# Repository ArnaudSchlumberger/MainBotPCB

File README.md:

# MainBotPCB

This project is part of Robot Télécom Strasbourg's work as part of our participation to the French Robot Cup.

See our Github page here: https://github.com/AssociationRobotTelecomStrasbourg

And our website (quite empty yet :/ ) here :https://associationrobottelecomstrasbourg.github.io/

MainBotPCB is the PCB that will contain the majority of the  components and connections required for our main robot to work, hence the original name :) .

NotesConception.md contains my notes while working on this project (in French)

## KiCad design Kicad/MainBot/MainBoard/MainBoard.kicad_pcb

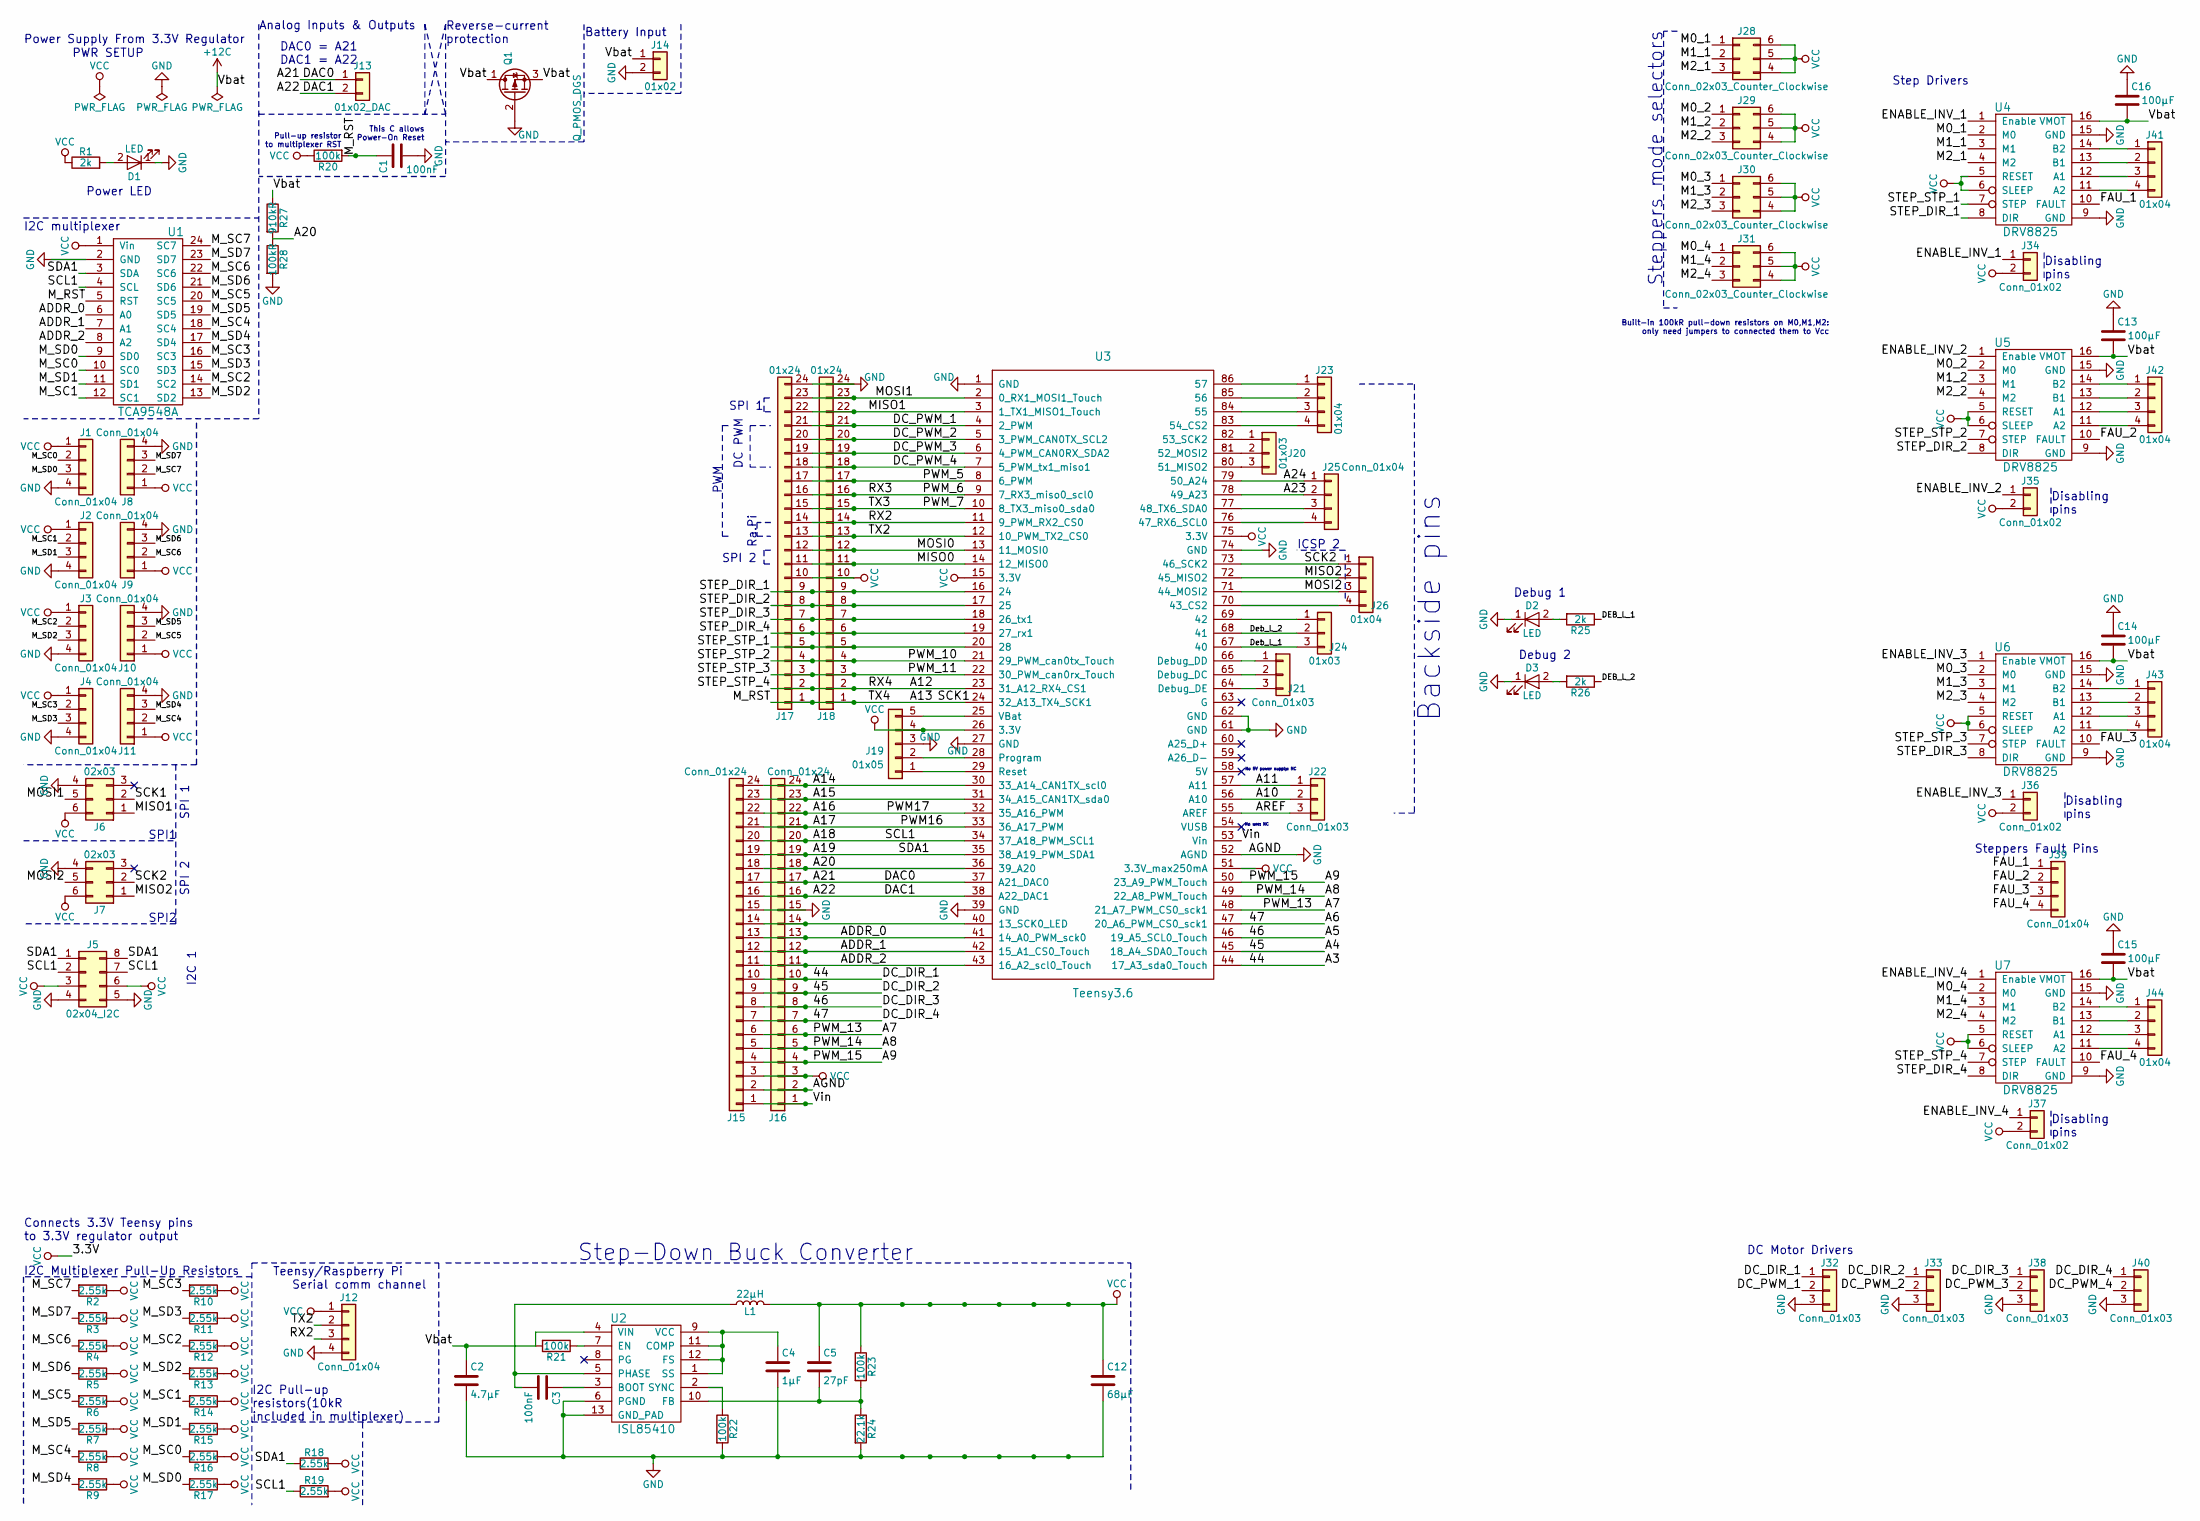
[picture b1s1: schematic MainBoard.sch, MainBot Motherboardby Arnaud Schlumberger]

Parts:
C1, C3: 100nF; C_1206_HandSoldering
C2: 4.7µF; C_1206_HandSoldering
C4: 1µF; C_1206_HandSoldering
C5: 27pF; C_1206_HandSoldering
C12: 68µF; CP_Elec_6.3x7.7
C13, C14, C15, C16: 100µF; CP_Radial_D6.3mm_P2.50mm
D1, D2, D3: LED; LED_1206
J1, J2, J3, J4, J8, J9, J10, J11, J12, J39: Conn_01x04; JST_XH_B04B-XH-A_04x2.50mm_Straight
J5: 02x04_I2C; Pin_Header_Straight_2x04_Pitch2.54mm
J6, J7: 02x03; Pin_Header_Straight_2x03_Pitch2.54mm
J13: 01x02_DAC; Pin_Header_Straight_1x02_Pitch2.54mm
J14: 01x02; BatConn
J15, J16: Conn_01x24; Socket_Strip_Straight_1x24_Pitch2.54mm
J17, J18: 01x24; Socket_Strip_Straight_1x24_Pitch2.54mm
J19: 01x05; Pin_Header_Straight_1x05_Pitch2.54mm
J20, J24: 01x03; Pin_Header_Straight_1x03_Pitch2.54mm
J21, J22: Conn_01x03; Pin_Header_Straight_1x03_Pitch2.54mm
J23, J26: 01x04; Pin_Header_Straight_1x04_Pitch2.54mm
J25: Conn_01x04; Pin_Header_Straight_1x04_Pitch2.54mm
J28, J29, J30, J31: Conn_02x03_Counter_Clockwise; Pin_Header_Straight_2x03_Pitch2.54mm
J32, J33, J38, J40: Conn_01x03; JST_XH_B03B-XH-A_03x2.50mm_Straight
J34, J35, J36, J37: Conn_01x02; Pin_Header_Straight_1x02_Pitch2.54mm
J41, J42, J43, J44: 01x04; JST_XH_B04B-XH-A_04x2.50mm_Straight
L1: 22µH; L1
Q1: Q_PMOS_DGS; SOT-23
R1, R25, R26: 2k; R_1206_HandSoldering
R2, R3, R4, R5, R6, R7, R8, R9, R10, R11, R12, R13, R14, R15, R16, R17, R18, R19: 2.55k; R_0805_HandSoldering
R20, R21, R22, R23: 100k; R_1206_HandSoldering
R24: 22.1k; R_1206_HandSoldering
R27: 910kR; R_1206_HandSoldering
R28: 100kR; R_1206_HandSoldering
U1: TCA9548A; TCA9548A_TSSOP
U2: ISL85410; DFN-12_DE-M
U3: Teensy3.6; Teensy35_36
U4, U5, U6, U7: DRV8825

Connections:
+12C: C2.1, C13.2, C14.2, C15.2, C16.2, J14.1, Q1.1 (D), Q1.3 (S), R21.2, R27.1, U2.4 (VIN), U4.16 (VMOT), U5.16 (VMOT), U6.16 (VMOT), U7.16 (VMOT)
/44: J15.10, J16.10, J32.1, U3.44 (17_A3_sda0_Touch)
/45: J15.9, J16.9, J33.1, U3.45 (18_A4_SDA0_Touch)
/46: J15.8, J16.8, J38.1, U3.46 (19_A5_SCL0_Touch)
/47: J15.7, J16.7, J40.1, U3.47 (20_A6_PWM_CS0_sck1)
/A7: J15.6, J16.6, U3.48 (21_A7_PWM_CS0_sck1)
/A8: J15.5, J16.5, U3.49 (22_A8_PWM_Touch)
/A9: J15.4, J16.4, U3.50 (23_A9_PWM_Touch)
/A10: J22.2, U3.56 (A10)
/A11: J22.1, U3.57 (A11)
/A12: J17.2, J18.2, U3.23 (31_A12_RX4_CS1), U7.7 (STEP)
/A13: C1.1, J6.2, J17.1, J18.1, R20.2, U1.5 (RST), U3.24 (32_A13_TX4_SCK1)
/A14: J15.24, J16.24, U3.30 (33_A14_CAN1TX_scl0)
/A15: J15.23, J16.23, U3.31 (34_A15_CAN1TX_sda0)
/A16: J15.22, J16.22, U3.32 (35_A16_PWM)
/A17: J15.21, J16.21, U3.33 (36_A17_PWM)
/A18: J5.2, J5.7, J15.20, J16.20, R19.1, U1.4 (SCL), U3.34 (37_A18_PWM_SCL1)
/A19: J5.1, J5.8, J15.19, J16.19, R18.1, U1.3 (SDA), U3.35 (38_A19_PWM_SDA1)
/A20: J15.18, J16.18, R27.2, R28.1, U3.36 (39_A20)
/A21: J13.1, J15.17, J16.17, U3.37 (A21_DAC0)
/A22: J13.2, J15.16, J16.16, U3.38 (A22_DAC1)
/A23: J25.2, U3.78 (49_A23)
/A24: J25.1, U3.79 (50_A24)
/ADDR_0: J15.13, J16.13, U1.6 (A0), U3.41 (14_A0_PWM_sck0)
/ADDR_1: J15.12, J16.12, U1.7 (A1), U3.42 (15_A1_CS0_Touch)
/ADDR_2: J15.11, J16.11, U1.8 (A2), U3.43 (16_A2_scl0_Touch)
/AREF: J22.3, U3.55 (AREF)
/DC_PWM_1: J17.21, J18.21, J32.2, U3.4 (2_PWM)
/DC_PWM_2: J17.20, J18.20, J33.2, U3.5 (3_PWM_CAN0TX_SCL2)
/DC_PWM_3: J17.19, J18.19, J38.2, U3.6 (4_PWM_CAN0RX_SDA2)
/DC_PWM_4: J17.18, J18.18, J40.2, U3.7 (5_PWM_tx1_miso1)
/DEB_L_1: J24.3, R25.1, U3.67 (40)
/DEB_L_2: J24.2, R26.1, U3.68 (41)
/ENABLE_INV_1: J34.1, U4.1 (Enable)
/ENABLE_INV_2: J35.1, U5.1 (Enable)
/ENABLE_INV_3: J36.1, U6.1 (Enable)
/ENABLE_INV_4: J37.1, U7.1 (Enable)
/FAU_1: J39.1, U4.10 (FAULT)
/FAU_2: J39.2, U5.10 (FAULT)
/FAU_3: J39.3, U6.10 (FAULT)
/FAU_4: J39.4, U7.10 (FAULT)
/M0_1: J28.1, U4.2 (M0)
/M0_2: J29.1, U5.2 (M0)
/M0_3: J30.1, U6.2 (M0)
/M0_4: J31.1, U7.2 (M0)
/M1_1: J28.2, U4.3 (M1)
/M1_2: J29.2, U5.3 (M1)
/M1_3: J30.2, U6.3 (M1)
/M1_4: J31.2, U7.3 (M1)
/M2_1: J28.3, U4.4 (M2)
/M2_2: J29.3, U5.4 (M2)
/M2_3: J30.3, U6.4 (M2)
/M2_4: J31.3, U7.4 (M2)
/MISO0: J17.11, J18.11, U3.14 (12_MISO0)
/MISO1: J6.1, J17.22, J18.22, U3.3 (1_TX1_MISO1_Touch)
/MISO2: J7.1, J26.2, U3.72 (45_MISO2)
/MOSI0: J17.12, J18.12, U3.13 (11_MOSI0)
/MOSI1: J6.5, J17.23, J18.23, U3.2 (0_RX1_MOSI1_Touch)
/MOSI2: J7.5, J26.3, U3.71 (44_MOSI2)
/M_SC0: J1.2, R16.2, U1.10 (SC0)
/M_SC1: J2.2, R14.2, U1.12 (SC1)
/M_SC2: J3.2, R12.2, U1.14 (SC2)
/M_SC3: J4.2, R10.2, U1.16 (SC3)
/M_SC4: J11.2, R8.2, U1.18 (SC4)
/M_SC5: J10.2, R6.2, U1.20 (SC5)
/M_SC6: J9.2, R4.2, U1.22 (SC6)
/M_SC7: J8.2, R2.2, U1.24 (SC7)
/M_SD0: J1.3, R17.2, U1.9 (SD0)
/M_SD1: J2.3, R15.2, U1.11 (SD1)
/M_SD2: J3.3, R13.2, U1.13 (SD2)
/M_SD3: J4.3, R11.2, U1.15 (SD3)
/M_SD4: J11.3, R9.2, U1.17 (SD4)
/M_SD5: J10.3, R7.2, U1.19 (SD5)
/M_SD6: J9.3, R5.2, U1.21 (SD6)
/M_SD7: J8.3, R3.2, U1.23 (SD7)
/PWM_5: J17.17, J18.17, U3.8 (6_PWM)
/PWM_6: J17.16, J18.16, U3.9 (7_RX3_miso0_scl0)
/PWM_7: J17.15, J18.15, U3.10 (8_TX3_miso0_sda0)
/PWM_10: J17.4, J18.4, U3.21 (29_PWM_can0tx_Touch), U5.7 (STEP)
/PWM_11: J17.3, J18.3, U3.22 (30_PWM_can0rx_Touch), U6.7 (STEP)
/RX2: J12.3, J17.14, J18.14, U3.11 (9_PWM_RX2_CS0)
/SCK2: J7.2, J26.1, U3.73 (46_SCK2)
/STEP_DIR_1: J17.9, J18.9, U3.16 (24), U4.8 (DIR)
/STEP_DIR_2: J17.8, J18.8, U3.17 (25), U5.8 (DIR)
/STEP_DIR_3: J17.7, J18.7, U3.18 (26_tx1), U6.8 (DIR)
/STEP_DIR_4: J17.6, J18.6, U3.19 (27_rx1), U7.8 (DIR)
/STEP_STP_1: J17.5, J18.5, U3.20 (28), U4.7 (STEP)
/TX2: J12.2, J17.13, J18.13, U3.12 (10_PWM_TX2_CS0)
/Vin: J15.1, J16.1, U3.53 (Vin)
GND: C1.2, C2.2, C4.2, C12.2, C13.1, C14.1, C15.1, C16.1, D1.1 (K), D2.1 (K), D3.1 (K), J1.4, J2.4, J3.4, J4.4, J5.4, J5.5, J6.4, J7.4, J8.4, J9.4, J10.4, J11.4, J12.4, J14.2, J15.2, J15.15, J16.2, J16.15, J17.24, J18.24, J19.3, J32.3, J33.3, J38.3, J40.3, Q1.2 (G), R22.2, R24.2, R28.2, U1.2 (GND), U2.6 (PGND), U2.13 (GND_PAD), U3.1 (GND), U3.27 (GND), U3.39 (GND), U3.52 (AGND), U3.61 (GND), U3.62 (GND), U3.74 (GND), U4.9 (GND), U4.15 (GND), U5.9 (GND), U5.15 (GND), U6.9 (GND), U6.15 (GND), U7.9 (GND), U7.15 (GND)
unnamed: C3.1, U2.3 (BOOT)
unnamed: C3.2, L1.1, U2.5 (PHASE)
unnamed: C4.1, U2.1 (SS), U2.9 (VCC), U2.11 (COMP), U2.12 (FS)
unnamed: C5.2, R23.2, R24.1, U2.10 (FB)
unnamed: D1.2 (A), R1.2
unnamed: D2.2 (A), R25.2
unnamed: D3.2 (A), R26.2
unnamed: J15.14, J16.14, U3.40 (13_SCK0_LED)
unnamed: J19.1, U3.29 (Reset)
unnamed: J19.2, U3.28 (Program)
unnamed: J19.5, U3.25 (VBat)
unnamed: J20.1, U3.82 (53_SCK2)
unnamed: J20.2, U3.81 (52_MOSI2)
unnamed: J20.3, U3.80 (51_MISO2)
unnamed: J21.1, U3.66 (Debug_DD)
unnamed: J21.2, U3.65 (Debug_DC)
unnamed: J21.3, U3.64 (Debug_DE)
unnamed: J23.1, U3.86 (57)
unnamed: J23.2, U3.85 (56)
unnamed: J23.3, U3.84 (55)
unnamed: J23.4, U3.83 (54_CS2)
unnamed: J24.1, U3.69 (42)
unnamed: J25.3, U3.77 (48_TX6_SDA0)
unnamed: J25.4, U3.76 (47_RX6_SCL0)
unnamed: J26.4, U3.70 (43_CS2)
unnamed: J41.1, U4.14 (B2)
unnamed: J41.2, U4.13 (B1)
unnamed: J41.3, U4.12 (A1)
unnamed: J41.4, U4.11 (A2)
unnamed: J42.1, U5.14 (B2)
unnamed: J42.2, U5.13 (B1)
unnamed: J42.3, U5.12 (A1)
unnamed: J42.4, U5.11 (A2)
unnamed: J43.1, U6.14 (B2)
unnamed: J43.2, U6.13 (B1)
unnamed: J43.3, U6.12 (A1)
unnamed: J43.4, U6.11 (A2)
unnamed: J44.1, U7.14 (B2)
unnamed: J44.2, U7.13 (B1)
unnamed: J44.3, U7.12 (A1)
unnamed: J44.4, U7.11 (A2)
unnamed: R21.1, U2.7 (EN)
unnamed: R22.1, U2.2 (SYNC)
VCC: C5.1, C12.1, J1.1, J2.1, J3.1, J4.1, J5.3, J5.6, J6.6, J7.6, J8.1, J9.1, J10.1, J11.1, J12.1, J15.3, J16.3, J17.10, J18.10, J19.4, J28.4, J28.5, J28.6, J29.4, J29.5, J29.6, J30.4, J30.5, J30.6, J31.4, J31.5, J31.6, J34.2, J35.2, J36.2, J37.2, L1.2, R1.1, R2.1, R3.1, R4.1, R5.1, R6.1, R7.1, R8.1, R9.1, R10.1, R11.1, R12.1, R13.1, R14.1, R15.1, R16.1, R17.1, R18.2, R19.2, R20.1, R23.1, U1.1 (Vin), U3.15 (3.3V), U3.26 (3.3V), U3.51 (3.3V_max250mA), U3.75 (3.3V), U4.5 (RESET), U4.6 (SLEEP), U5.5 (RESET), U5.6 (SLEEP), U6.5 (RESET), U6.6 (SLEEP), U7.5 (RESET), U7.6 (SLEEP)

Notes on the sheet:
Power Supply From 3.3V Regulator
PWR SETUP
Step Drivers
DC Motor Drivers
Teensy/Raspberry Pi Serial comm channel
I2C multiplexer
I2C Pull-up resistors(10kR included in multiplexer)
Connects 3.3V Teensy pins to 3.3V regulator output
ICSP 2
SPI2
SPI1
I2C Multiplexer Pull-Up Resistors
DAC0 = A21 DAC1 = A22
Analog Inputs & Outputs
PWM
DC PWM
Ra.Pi
SPI 1
SPI 2
SPI 1
I2C 1
Disabling pins
Power LED
Steppers Fault Pins
Debug 1
Debug 2
Backside pins
No 5V power supply: NC
No use: NC
Pull-up resistor to multiplexer RST
Built-in 100kR pull-down resistors on M0,M1,M2: only need jumpers to connected them to Vcc
Steppers mode selectors
Battery Input
Step-Down Buck Converter
This C allows Power-On Reset
Reverse-current protection

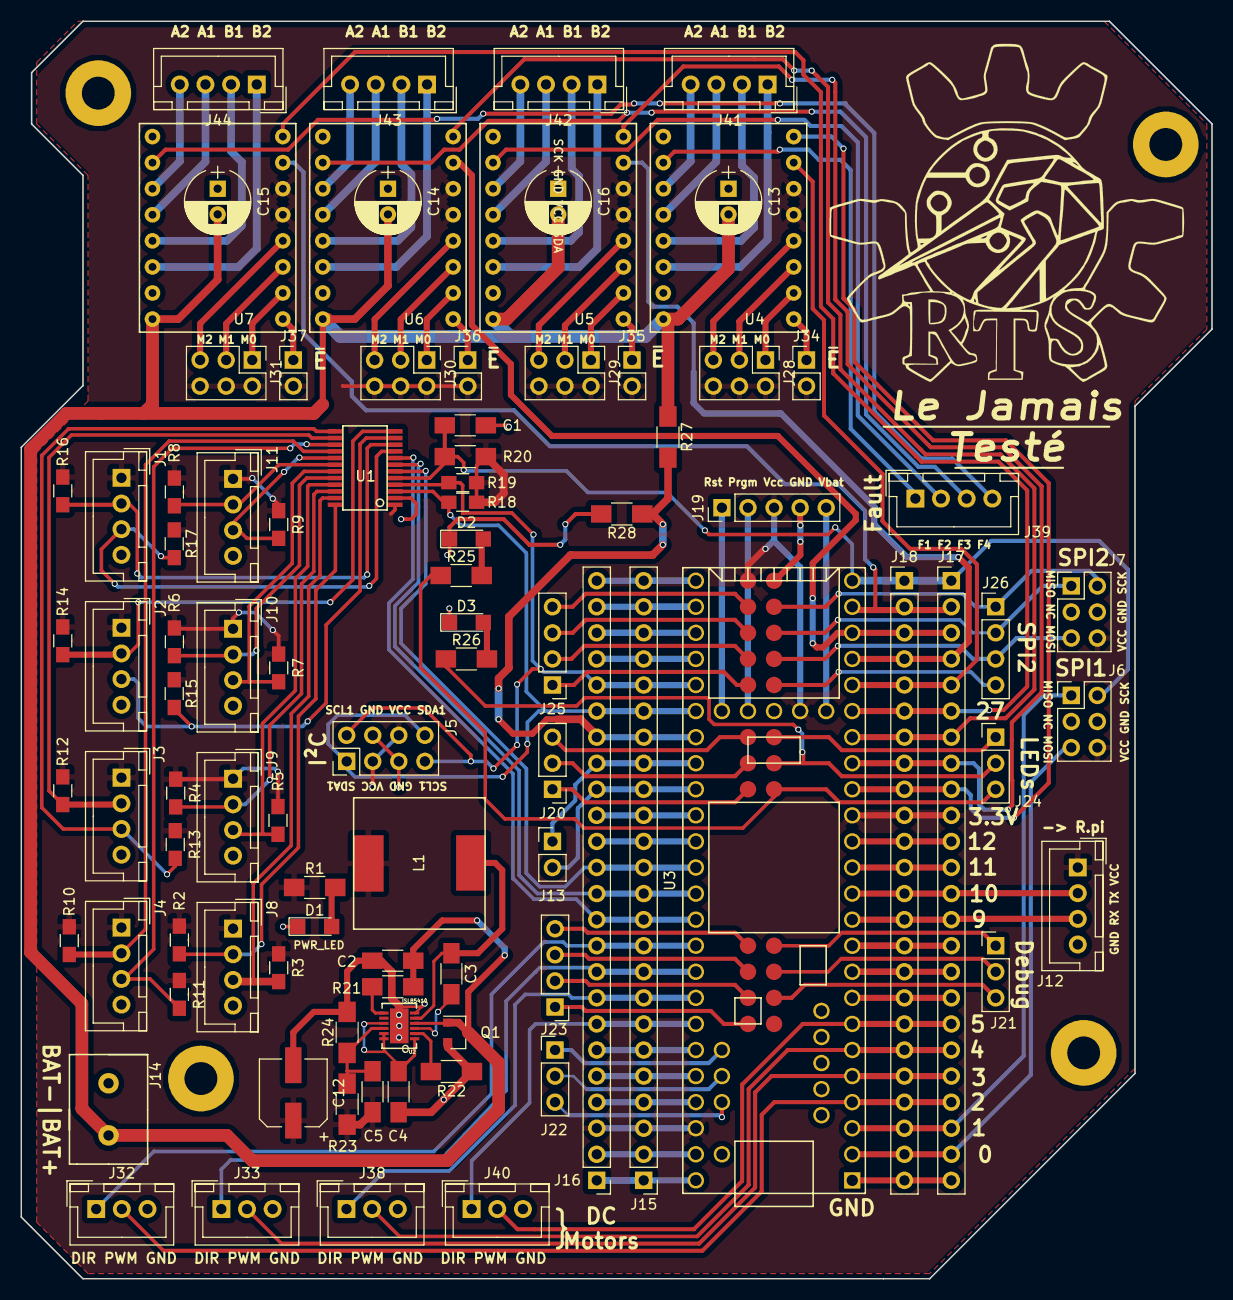
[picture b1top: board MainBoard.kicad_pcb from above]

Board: 2 copper layers, 116.0 x 122.5 mm, 93 parts (0 on the bottom side), 134 nets.

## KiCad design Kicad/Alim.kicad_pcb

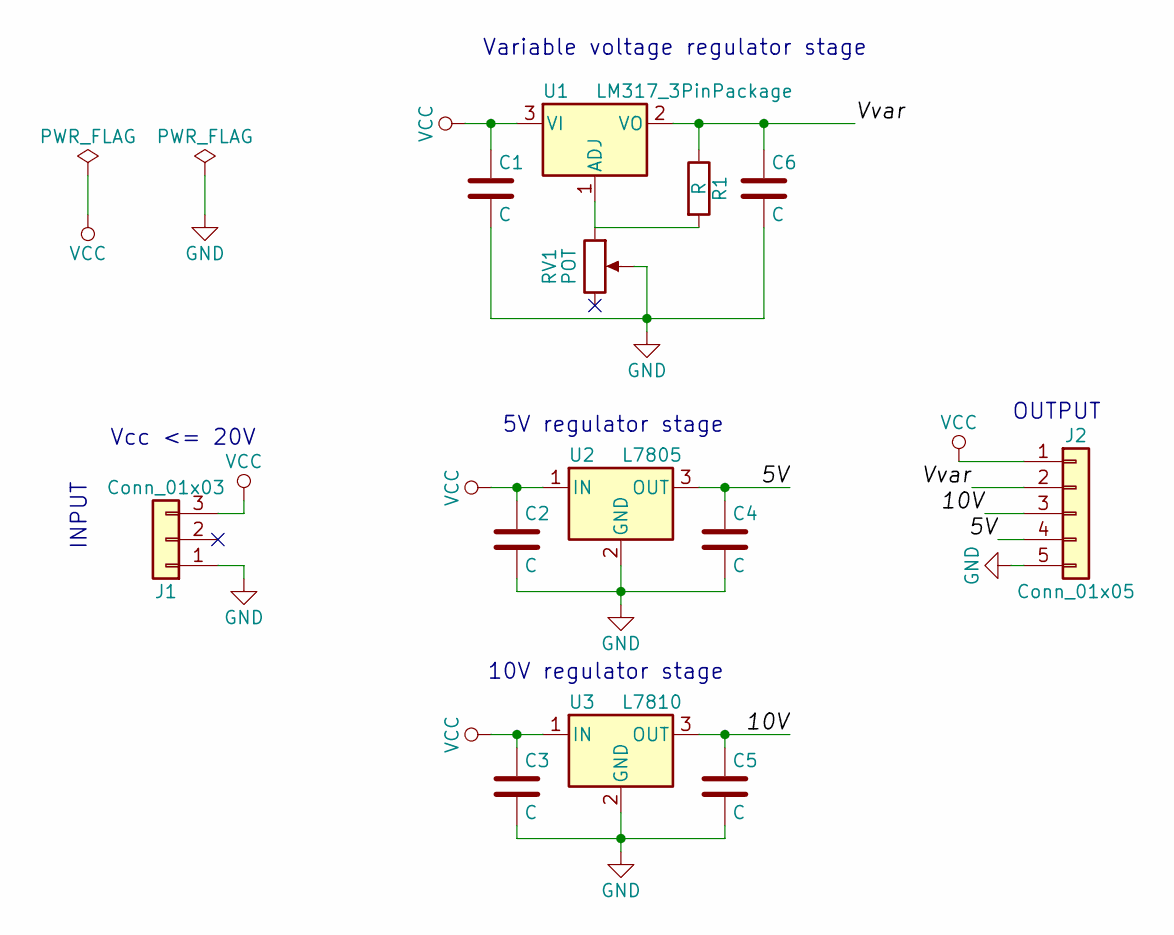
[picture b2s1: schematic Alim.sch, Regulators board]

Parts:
C1, C2, C3, C4, C5, C6: C; C_Disc_D4.7mm_W2.5mm_P5.00mm
J1: Conn_01x03; Pin_Header_Straight_1x03_Pitch2.54mm
J2: Conn_01x05; Pin_Header_Straight_1x05_Pitch2.54mm
R1: R; R_Axial_DIN0207_L6.3mm_D2.5mm_P7.62mm_Horizontal
RV1: POT; Potentiometer_Alps_RK09Y_Vertical
U1: LM317_3PinPackage; TO-220
U2: L7805; TO-220
U3: L7810; TO-220

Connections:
/5V: C4.1, J2.4, U2.3 (OUT)
/10V: C5.1, J2.3, U3.3 (OUT)
/Vvar: C6.1, J2.2, R1.1, U1.2 (VO)
GND: C1.2, C2.2, C3.2, C4.2, C5.2, C6.2, J1.1, J2.5, RV1.2, U2.2 (GND), U3.2 (GND)
unnamed: R1.2, RV1.1, U1.1 (ADJ)
VCC: C1.1, C2.1, C3.1, J1.3, J2.1, U1.3 (VI), U2.1 (IN), U3.1 (IN)

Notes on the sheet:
Variable voltage regulator stage
5V regulator stage
10V regulator stage
INPUT
Vcc <= 20V
OUTPUT

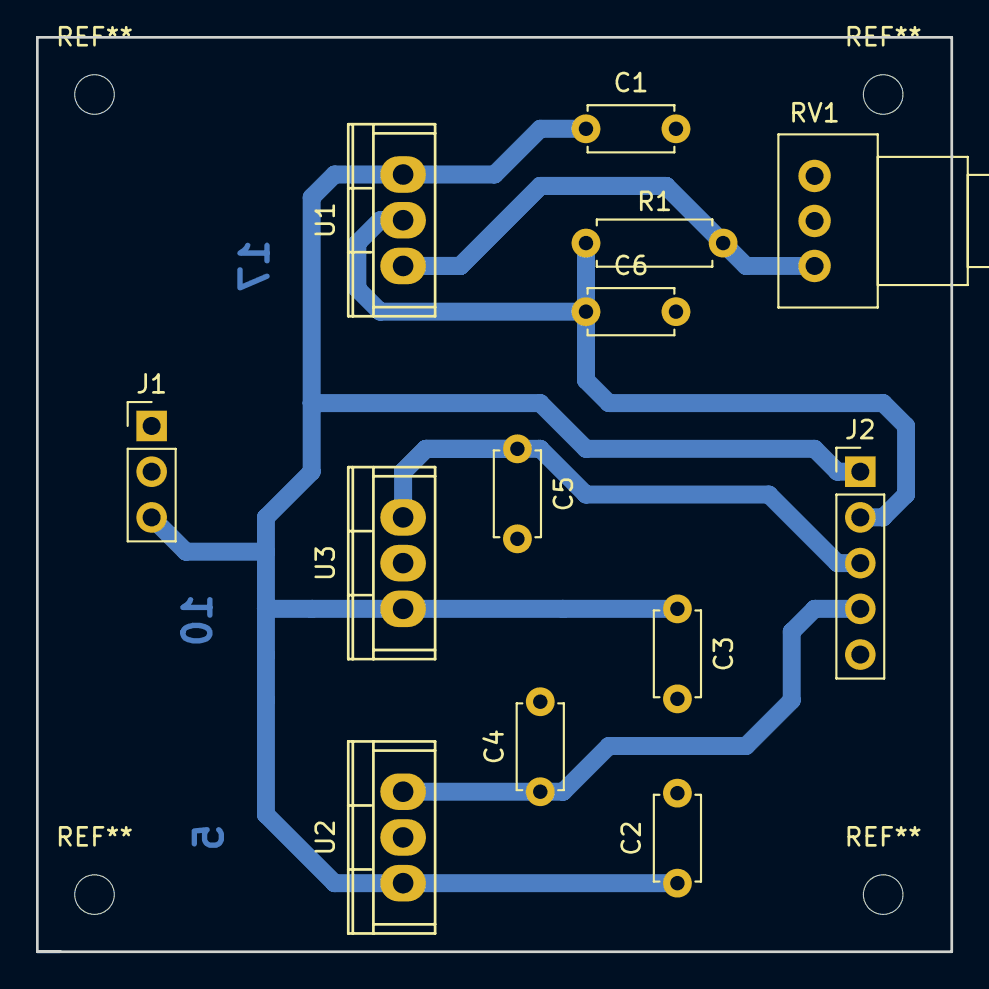
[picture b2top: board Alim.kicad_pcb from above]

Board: 2 copper layers, 50.8 x 50.8 mm, 13 parts (0 on the bottom side), 6 nets.

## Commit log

2019-02-02 Setting everything up
2019-02-02 Cleaning things up
2019-02-02 Uploading my notes
2019-02-02 Notes update
2019-02-02 Library Migration
2019-02-02 First schematic PDF export
2019-02-02 Schematic update
2019-02-02 README.md update
2019-02-07 Ajout Comm Série Rasp/Teensy
2019-02-07 Added I2C pull-up resistor, I2C multiplexer
2019-02-11 Finished female headers
2019-02-11 Added multiplexer and driver footprint, updated PCB
2019-02-11 Added notes on schematic
2019-02-12 Added capacitors to regulator, ICSP2 pins, completed I2C Vcc and GND connections
2019-02-12 Added SPI1 and SPI2 channels
2019-02-12 Finished Multiplexer output, added pulled up resistors to multiplexer output
2019-02-12 Removed NC on DRV8825 Step drivers
2019-02-12 Removed NC on FAULT pins of Step drivers
2019-02-12 Updated .pdf preview
2019-02-13 Added Analog INs and OUTs
2019-02-13 Increased Schematic Size
2019-02-16 Added stepper drivers' capacitors values
2019-02-16 Deleted PWM and analog blocks
2019-02-16 Connected TCA4598A's ADDR pins to Teensy, Connected DC Drivers' PWM pins to Teensy
2019-02-16 Switched Serial communication channel from RX1/TX1 to RX2/TX2, Deleted unused labels
2019-02-16 Connected DC drivers pins to Teensy
2019-02-20 Added mode selectors for DRV8825 in the form of jumper connectors
2019-02-20 Added jumpers to disable DRV8825 Stepper drivers
2019-02-20 Added AREF selector
2019-02-27 Connected Steppers Sleep and Reset pins to Vcc
2019-03-01 Connected Steppers STP & DIR to Teensy
2019-03-01 Added external connectors to Steppers Fault pins
2019-03-01 Added DAC0 and DAC1 labels
2019-03-01 Connected backside pins to headers
2019-03-01 Added notes
2019-03-01 Added Serial channel to Dynamixel actuators, connected debug LEDs to Teensy
2019-03-01 Updated pdf
2019-03-03 Removed Dynamixel connectors
2019-03-03 Redesigned Steppers' mode selectors
2019-03-03 Corrected multiplexer connectors to slaves
2019-03-03 Added pull-up resistor to multiplexer RST pin
2019-03-03 Corrected Steppers' mode selectors
2019-03-03 Connected multiplexer RST to Teensy through pin 32
2019-03-03 Corrected Rpi/Teensy Serial Channel: added VCC and GND
2019-03-03 Added Design report
2019-03-06 Corrected Reverse-current protection, replaced regulator with 3.3V Step-Down Buck Converter
2019-03-06 Updated schematic pdf
2019-03-06 Library corrections: added pins numbers
2019-03-08 Corrections and started PCB
2019-03-12 So much things :)
2019-03-16 Small details
